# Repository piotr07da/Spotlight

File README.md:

# Spotlight
Spotlight is a project of a device used to highlight targets on a shooting range. This is achieved by using a beam of light that cycles between different targets. The light can be turned on and off, ramped up or down, or turned to strobe mode.

# Projects
There are three projects in this repository.

## Spotlight
The Spotlight project is a C++ project that consists main software used in the device.

## SpotlightMainCircuit
The SpotlightMainCircuit is a KiCad project of the device's circuit board.

## SpotlightDesktopClient
The SpotlightDesktopClient project is an Electron project written in TypeScript. It is used to connect with the device for diagnostic purposes, mainly for debugging the sound trigger feature of the device.

# Hardware
The Spotlight is build of:
- Main unit. This contains a Particle Photon device, stepper motor controler, voltage regulators, operation amplifiers, and a microphone.
- Controller with buttons and display. This allows the user to configure a sequence of targets to highlight.
- Light unit. This consists of a power LED mounted on a shaft of a stepper motor. It can be pointed at any direction.

# How to use it

## Configuration

### Controller
To configure the device we use controller unit.
```
 _____________________________________________
|                                             |
|         __________________                  |
|   /\   |                  |       /\        |
|   ||   |                  |       ||        |
|        |                  |   <==    ==>    |
|   ||   |                  |       ||        |
|   \/   |__________________|       \/        |
|                                             |
|_____________________________________________|
```

There is a display in the middle of the controller.

There are two buttons on the left:
- UP - if applicable it directly jumps to the previous spot (target), staying in the same setting (for example direction of light)
- DOWN - if applicable it directly jumps to the next spot (target), staying in the same setting

There are four buttons on the right:
- UP - used to select the previous position in the menu
- DOWN - used to select the next position in the menu
- LEFT - exits from the current menu position
- RIGHT - enters the selected menu position

### How to configure
First we need to configure a number of spots (shooting targets). We do that by going to the Global Options (select it using UP/DOWN arrows on the right). After selecting Global Options enter it (using RIGHT arrow on the right).
After that we can exit to the main menu using LEFT arrow on the right.
No we can select Spots menu option and enter it. In this menu we can switch between different spots using arrows on the left.
To configure a spot we need to enter one of the available settings:
- Direction - this setting allows to use UP and DOWN arrows to physically rotate the light. To make it easy the light will be turned on automatically to allow to direct it precisly at the target
- Spot Time - this setting tells for how many milliseconds the light will be directed at the target
- Spot Activity - this setting tells how the light will behave. There are different modes:
  - turned on
  - turned off
  - ramping from off to on
  - ramping from on to off
  - ramping from off through on and again to off
  - ramping from on through off and again to on
  - strobe
- Travel Time - this setting tells how much time it will take for the light to turn toward desingated direction
- Travel Activity - this setting tells how light will behave during the travel (the same light behaviors as in Spot Activity option)

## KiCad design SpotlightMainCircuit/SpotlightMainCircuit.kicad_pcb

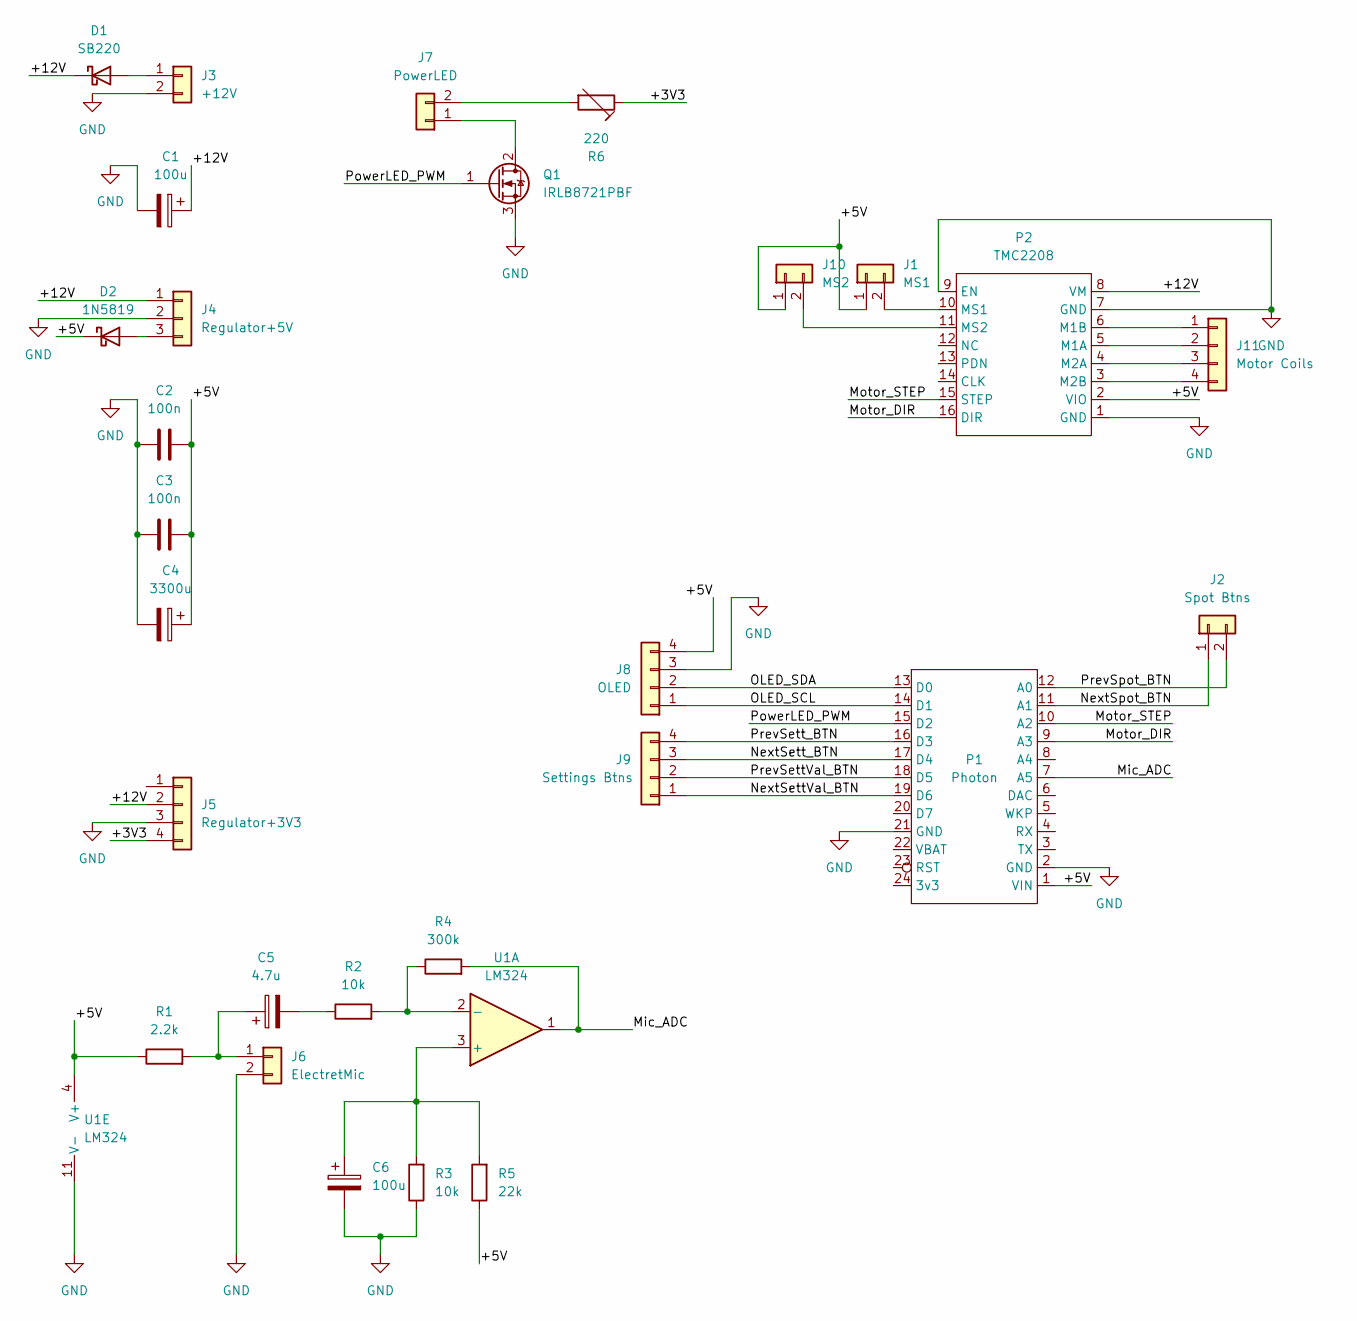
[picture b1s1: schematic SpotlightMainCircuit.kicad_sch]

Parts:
C1, C6: 100u; CP_Radial_D5.0mm_P2.00mm
C2, C3: 100n; C_Disc_D5.0mm_W2.5mm_P2.50mm
C4: 3300u; CP_Radial_D10.0mm_P5.00mm
C5: 4.7u; CP_Radial_D5.0mm_P2.00mm
D1: SB220; D_DO-41_SOD81_P10.16mm_Horizontal
D2: 1N5819; D_DO-41_SOD81_P10.16mm_Horizontal
J1: MS1; PinHeader_1x02_P2.54mm_Vertical
J2: Spot Btns; PinHeader_1x02_P2.54mm_Horizontal
J3: +12V; PinHeader_1x02_P2.54mm_Horizontal
J4: Regulator+5V; PinHeader_1x03_P2.54mm_Vertical
J5: Regulator+3V3; PinHeader_1x04_P2.54mm_Vertical
J6: ElectretMic; PinHeader_1x02_P2.54mm_Horizontal
J7: PowerLED; PinHeader_1x02_P2.54mm_Horizontal
J8: OLED; PinHeader_1x04_P2.54mm_Horizontal
J9: Settings Btns; PinHeader_1x04_P2.54mm_Horizontal
J10: MS2; PinHeader_1x02_P2.54mm_Vertical
J11: Motor Coils; PinHeader_1x04_P2.54mm_Horizontal
P1: Photon; ParticlePhoton
P2: TMC2208
Q1: IRLB8721PBF; TO-220-3_Vertical
R1: 2.2k; R_Axial_DIN0204_L3.6mm_D1.6mm_P2.54mm_Vertical
R2: 10k; R_Axial_DIN0204_L3.6mm_D1.6mm_P7.62mm_Horizontal
R3: 10k; R_Axial_DIN0204_L3.6mm_D1.6mm_P2.54mm_Vertical
R4: 300k; R_Axial_DIN0204_L3.6mm_D1.6mm_P2.54mm_Vertical
R5: 22k; R_Axial_DIN0204_L3.6mm_D1.6mm_P2.54mm_Vertical
R6: 220; Potentiometer_Piher_PT-10-V05_Vertical
U1: LM324; DIP-14_W7.62mm_LongPads

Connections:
/+3V3: J5.4, R6.1
/+5V: C2.2, C3.2, C4.1, D2.1 (K), J1.1, J8.4, J10.1, P1.1 (VIN), P2.2 (VIO), R1.1, R5.1, U1.4 (V+)
/+12V: C1.1, D1.1 (K), J4.1, J5.2, P2.8 (VM)
/Mic_ADC: P1.7 (A5), R4.2, U1.1
/Motor_DIR: P1.9 (A3), P2.16 (DIR)
/Motor_STEP: P1.10 (A2), P2.15 (STEP)
/NextSettVal_BTN: J9.1, P1.19 (D6)
/NextSett_BTN: J9.3, P1.17 (D4)
/NextSpot_BTN: J2.1, P1.11 (A1)
/OLED_SCL: J8.1, P1.14 (D1)
/OLED_SDA: J8.2, P1.13 (D0)
/PowerLED_PWM: P1.15 (D2), Q1.1 (G)
/PrevSettVal_BTN: J9.2, P1.18 (D5)
/PrevSett_BTN: J9.4, P1.16 (D3)
/PrevSpot_BTN: J2.2, P1.12 (A0)
GND: C1.2, C2.1, C3.1, C4.2, C6.2, J3.2, J4.2, J5.3, J6.2, J8.3, P1.2 (GND), P1.21 (GND), P2.1 (GND), P2.7 (GND), P2.9 (EN), Q1.3 (S), R3.1, U1.11 (V-)
unnamed: C5.1, J6.1, R1.2
unnamed: C5.2, R2.1
unnamed: C6.1, R3.2, R5.2, U1.3 (+)
unnamed: D1.2 (A), J3.1
unnamed: D2.2 (A), J4.3
unnamed: J1.2, P2.10 (MS1)
unnamed: J7.1, Q1.2 (D)
unnamed: J7.2, R6.2
unnamed: J11.4, P2.3 (M2B)
unnamed: J11.3, P2.4 (M2A)
unnamed: J11.2, P2.5 (M1A)
unnamed: J11.1, P2.6 (M1B)
unnamed: J10.2, P2.11 (MS2)
unnamed: R2.2, R4.1, U1.2 (-)

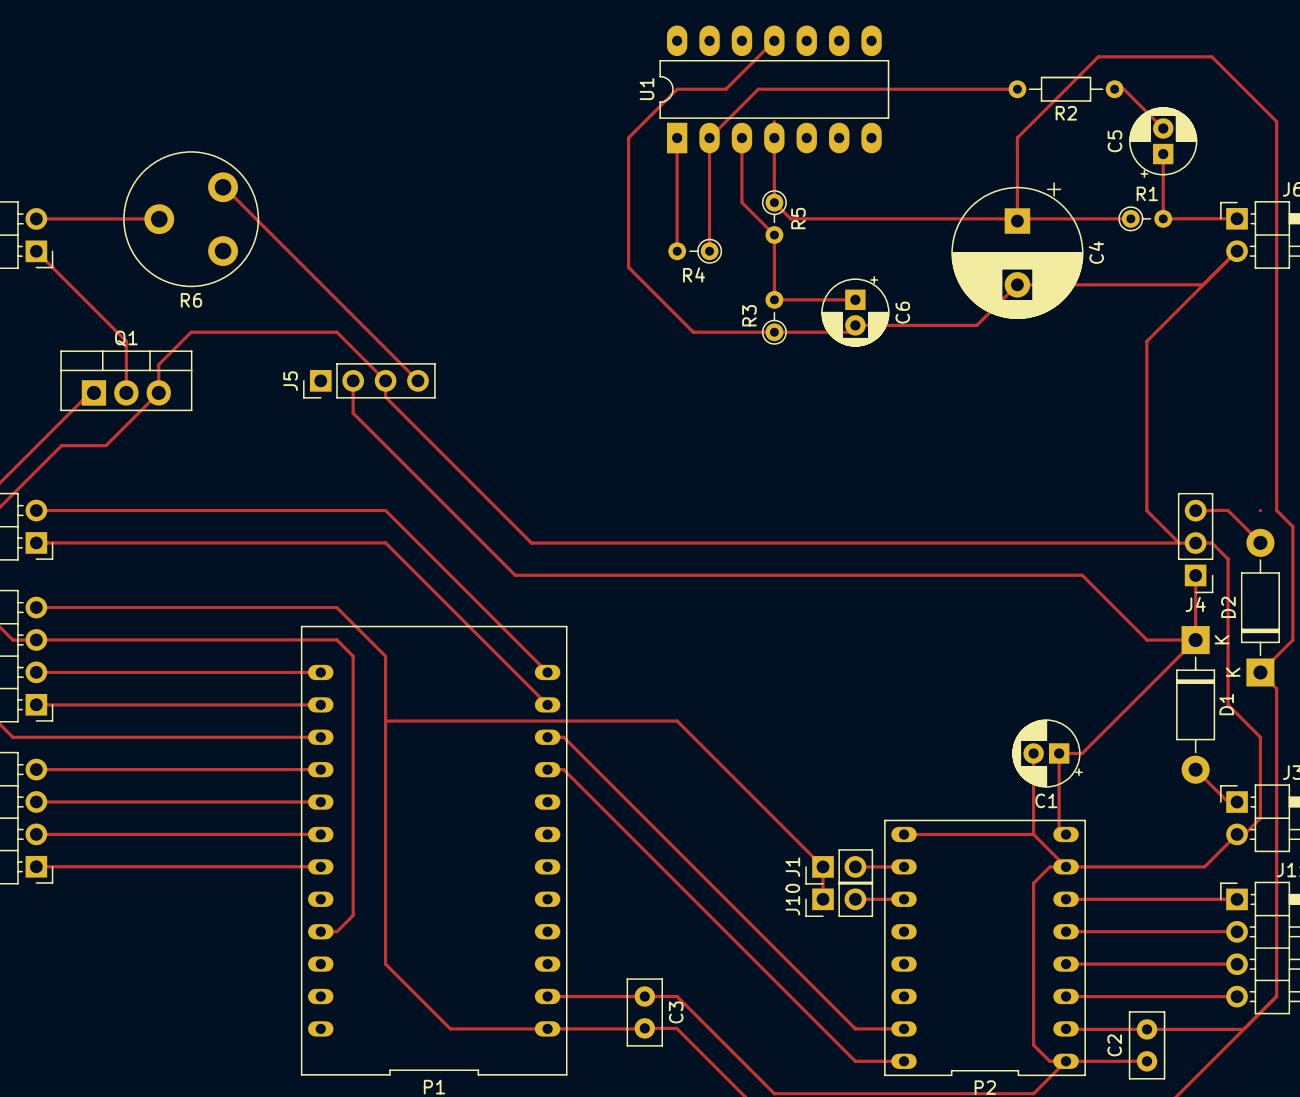
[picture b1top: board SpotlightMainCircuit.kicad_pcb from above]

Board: 2 copper layers, 29 parts (0 on the bottom side), 30 nets.

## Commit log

2021-12-27 no message
2021-12-27 init
2021-12-27 interfaces
2021-12-27 compiles
2021-12-28 all settings
2021-12-28 display - change lib to adafruit_sh1106
2021-12-28 zabezpieczenie przed redefinicją biblioteki Adafruit SH1106
2021-12-29 display fixes
2021-12-30 user interface
2021-12-30 button fix
2021-12-31 stepper motor
2021-12-31 LightActivity light implementations
2022-01-01 events
2022-01-01 photon failed
2022-01-01 after refactor
2022-01-01 Runner interface
2022-01-01 Runner
2022-01-02 removing AccelStepper
2022-01-03 Motor - in progress
2022-01-03 named buttons
2022-01-03 Button - IsReleased
2022-01-03 Standby mode
2022-01-03 Runner - trave time bottom limitation
2022-01-08 pins
2022-01-10 audio input
2022-01-15 motor fixes
2022-01-15 possible mem leak fix
2022-01-15 sending audio data through tcp
2022-01-16 without dynamic memory allocation
2022-01-16 fixed issue with loosing speed accuracy after around 30 minutes of running
2022-01-19 SpotlightDesktopClient
2022-01-19 SpotlightDesktopClient - communication protocol done
2022-01-27 AudioTrigger in progress
2022-01-27 Spectrum
2022-01-28 AudioTrigger - algo in progress
2022-01-29 AudioTrigger
2022-01-30 ADC PWM conflict
2022-01-30 Solved ADC PWM conflict - changed timer from TIM3 to TIM2
2022-01-30 better strobe
2022-01-30 new menu system - POC
2022-01-30 new menu system
2022-01-30 new menu system - done
2022-02-01 even better menu
2022-02-01 menu improvment and minor fixes
2022-02-01 AudioTrigger fixed
2022-02-01 prettier display
2022-02-01 valueDelta calculation imporved
2022-02-02 button pulldown fix
2022-02-02 disable wifi connection at start
2022-11-30 useful comments
2023-03-23 Create LICENSE
